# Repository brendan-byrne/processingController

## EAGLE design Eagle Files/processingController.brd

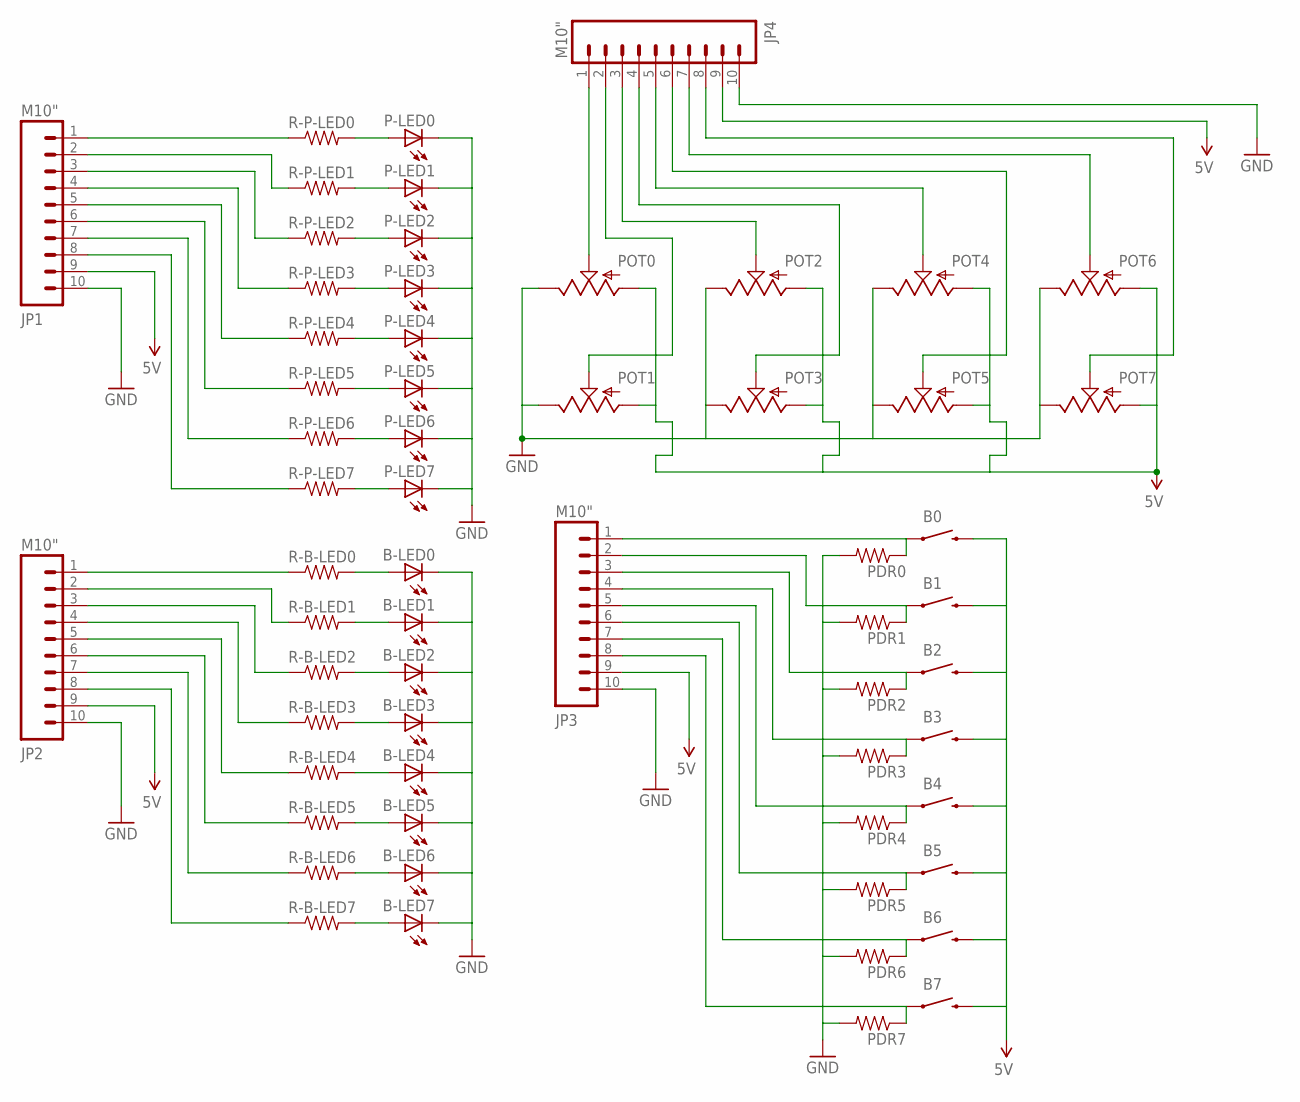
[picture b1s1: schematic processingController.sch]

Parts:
B0, B1, B2, B3, B4, B5, B6, B7: SWITCH-MOMENTARY-212MM; TACTILE-PTH-12MM
B-LED0, B-LED1, B-LED2, B-LED3, B-LED4, B-LED5, B-LED6, B-LED7: LED3MM
JP1, JP2, JP3, JP4: M10"; 1X10
P-LED0, P-LED1, P-LED2, P-LED3, P-LED4, P-LED5, P-LED6, P-LED7: LED3MM
PDR0, PDR1, PDR2, PDR3, PDR4, PDR5, PDR6, PDR7: RESISTOREZ; AXIAL-0.3EZ
POT0, POT1, POT2, POT3, POT4, POT5, POT6, POT7: POT; ALPS_POT
R-B-LED0, R-B-LED1, R-B-LED2, R-B-LED3, R-B-LED4, R-B-LED5, R-B-LED6, R-B-LED7: RESISTOREZ; AXIAL-0.3EZ
R-P-LED0, R-P-LED1, R-P-LED2, R-P-LED3, R-P-LED4, R-P-LED5, R-P-LED6, R-P-LED7: RESISTOREZ; AXIAL-0.3EZ

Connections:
5V: B0.3 (2), B1.3 (2), B2.3 (2), B3.3 (2), B4.3 (2), B5.3 (2), B6.3 (2), B7.3 (2), JP1.9, JP2.9, JP3.9, JP4.9, POT0.P$3 (A), POT1.P$3 (A), POT2.P$3 (A), POT3.P$3 (A), POT4.P$3 (A), POT5.P$3 (A), POT6.P$3 (A), POT7.P$3 (A)
GND: B-LED0.K (C), B-LED1.K (C), B-LED2.K (C), B-LED3.K (C), B-LED4.K (C), B-LED5.K (C), B-LED6.K (C), B-LED7.K (C), JP1.10, JP2.10, JP3.10, JP4.10, P-LED0.K (C), P-LED1.K (C), P-LED2.K (C), P-LED3.K (C), P-LED4.K (C), P-LED5.K (C), P-LED6.K (C), P-LED7.K (C), PDR0.P$2 (2), PDR1.P$2 (2), PDR2.P$2 (2), PDR3.P$2 (2), PDR4.P$2 (2), PDR5.P$2 (2), PDR6.P$2 (2), PDR7.P$2 (2), POT0.P$1 (E), POT1.P$1 (E), POT2.P$1 (E), POT3.P$1 (E), POT4.P$1 (E), POT5.P$1 (E), POT6.P$1 (E), POT7.P$1 (E)
unnamed: P-LED0.A, R-P-LED0.P$2 (2)
unnamed: P-LED1.A, R-P-LED1.P$2 (2)
unnamed: P-LED2.A, R-P-LED2.P$2 (2)
unnamed: P-LED3.A, R-P-LED3.P$2 (2)
unnamed: P-LED4.A, R-P-LED4.P$2 (2)
unnamed: P-LED5.A, R-P-LED5.P$2 (2)
unnamed: P-LED6.A, R-P-LED6.P$2 (2)
unnamed: P-LED7.A, R-P-LED7.P$2 (2)
unnamed: B-LED1.A, R-B-LED1.P$2 (2)
unnamed: B-LED2.A, R-B-LED2.P$2 (2)
unnamed: B-LED3.A, R-B-LED3.P$2 (2)
unnamed: B-LED4.A, R-B-LED4.P$2 (2)
unnamed: B-LED5.A, R-B-LED5.P$2 (2)
unnamed: B-LED6.A, R-B-LED6.P$2 (2)
unnamed: B-LED7.A, R-B-LED7.P$2 (2)
unnamed: B-LED0.A, R-B-LED0.P$2 (2)
unnamed: JP1.1, R-P-LED0.P$1 (1)
unnamed: JP1.2, R-P-LED1.P$1 (1)
unnamed: JP1.3, R-P-LED2.P$1 (1)
unnamed: JP1.4, R-P-LED3.P$1 (1)
unnamed: JP1.5, R-P-LED4.P$1 (1)
unnamed: JP1.6, R-P-LED5.P$1 (1)
unnamed: JP1.7, R-P-LED6.P$1 (1)
unnamed: JP1.8, R-P-LED7.P$1 (1)
unnamed: JP4.1, POT0.P$2 (S)
unnamed: JP2.1, R-B-LED0.P$1 (1)
unnamed: JP2.2, R-B-LED1.P$1 (1)
unnamed: JP2.3, R-B-LED2.P$1 (1)
unnamed: JP2.4, R-B-LED3.P$1 (1)
unnamed: JP2.5, R-B-LED4.P$1 (1)
unnamed: JP2.6, R-B-LED5.P$1 (1)
unnamed: JP2.7, R-B-LED6.P$1 (1)
unnamed: JP2.8, R-B-LED7.P$1 (1)
unnamed: JP4.3, POT2.P$2 (S)
unnamed: JP4.5, POT4.P$2 (S)
unnamed: JP4.7, POT6.P$2 (S)
unnamed: JP4.2, POT1.P$2 (S)
unnamed: JP4.4, POT3.P$2 (S)
unnamed: JP4.6, POT5.P$2 (S)
unnamed: JP4.8, POT7.P$2 (S)
PDR0: B0.1, JP3.1, PDR0.P$1 (1)
PDR1: B1.1, JP3.2, PDR1.P$1 (1)
PDR2: B2.1, JP3.3, PDR2.P$1 (1)
PDR3: B3.1, JP3.4, PDR3.P$1 (1)
PDR4: B4.1, JP3.5, PDR4.P$1 (1)
PDR5: B5.1, JP3.6, PDR5.P$1 (1)
PDR6: B6.1, JP3.7, PDR6.P$1 (1)
PDR7: B7.1, JP3.8, PDR7.P$1 (1)

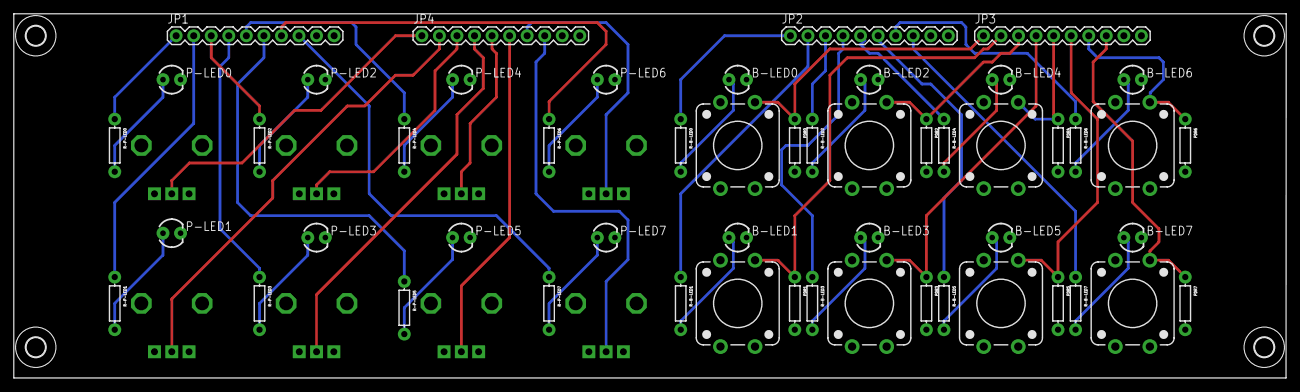
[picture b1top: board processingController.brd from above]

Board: 2 copper layers, 184.2 x 52.7 mm, 64 parts (0 on the bottom side), 50 nets.

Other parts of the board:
U$1, U$2, U$3, U$4: 2,8

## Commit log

2014-03-07 First Upload
    Raw firmware and first draft for layouot
2014-03-12 SH*T does not work
2014-03-14 The code works on micro pro
    Input it is set on A10
2014-03-17 Hi, brendan, finally it kind of works! shame on me !
2014-03-17 Arduino Byte Send
2014-03-17 Quick Fix

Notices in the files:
parts and their libraries:
SparkFun-Electromechanical: Licensing: CC v3.0 Share-Alike You are welcome to use this library for commercial purposes.
